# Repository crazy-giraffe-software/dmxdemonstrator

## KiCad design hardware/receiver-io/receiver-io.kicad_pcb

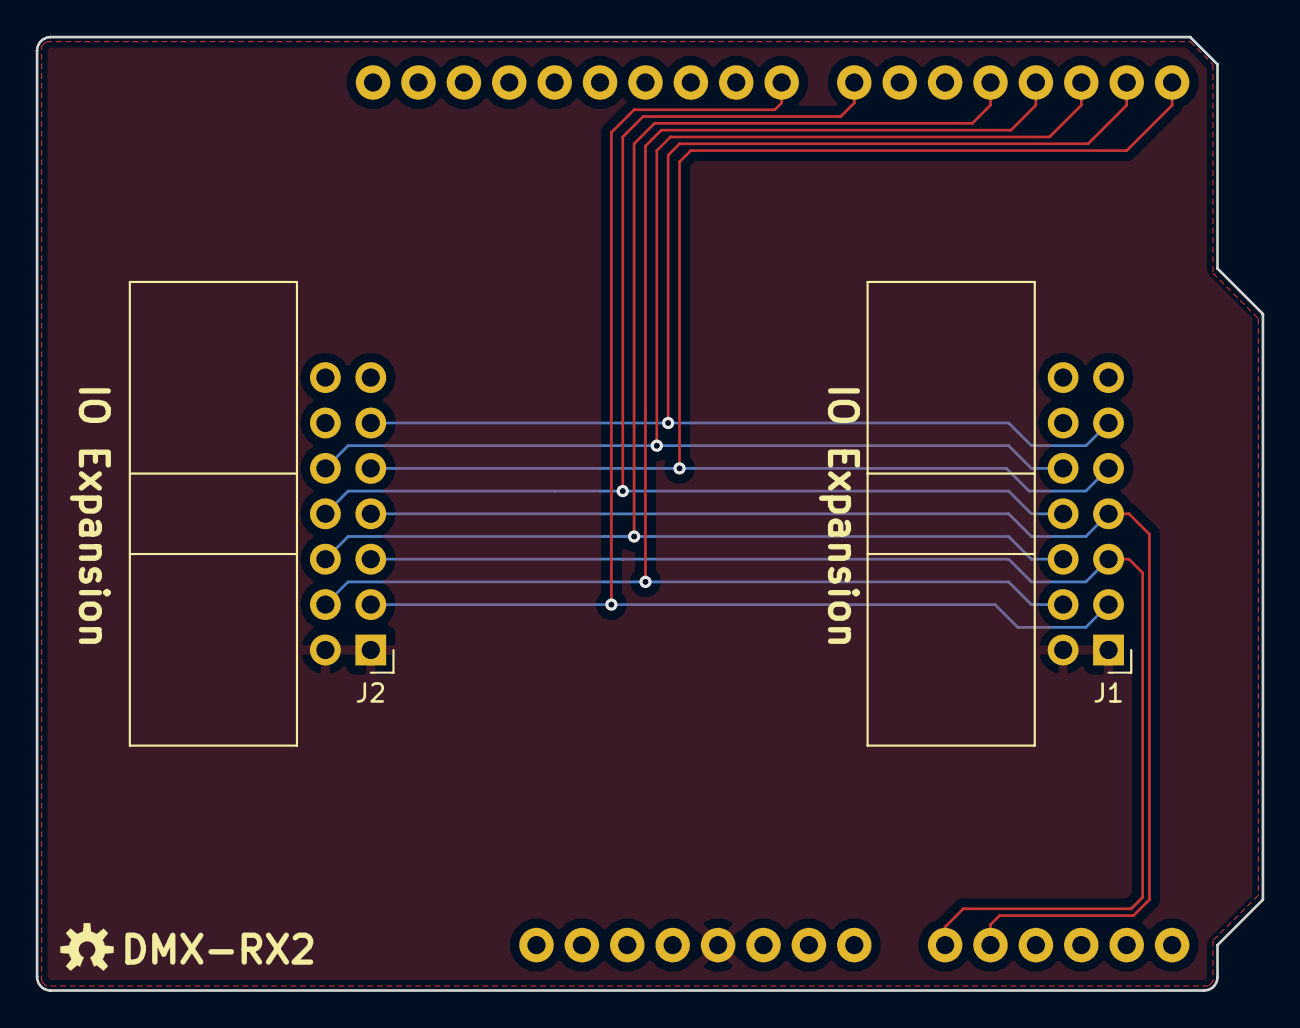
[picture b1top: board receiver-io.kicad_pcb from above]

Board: 2 copper layers, 68.6 x 53.3 mm, 3 parts (0 on the bottom side), 11 nets.

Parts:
A1: Arduino_UNO_R3; ARDUINO_R3_NO_HOLES
J1, J2: IO EXTENSION; IDC-Header_2x07_P2.54mm_Horizontal

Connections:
+5V: A1.5, J1.1, J1.2, J2.1, J2.2
/A0: A1.9, J1.5, J2.5
/A1: A1.10, J1.7, J2.7
/DMX-DIR: A1.17, J1.10, J2.10
/DMX-RX: A1.15, J1.9, J2.9
/DMX-TX: A1.16, J1.11, J2.11
/SR-CLK: A1.19, J1.6, J2.6
/SR-OUT: A1.18, J1.4, J2.4
/~SR_CLR: A1.22, J1.8, J2.8
/~WR: A1.23, J1.3, J2.3
GND: A1.6, A1.7, A1.29, J1.13, J1.14, J2.13, J2.14

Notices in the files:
hardware/receiver-io/receiver-io.kicad_pcb:
Released under the Creative Commons Attribution Share-Alike 4.0 License
